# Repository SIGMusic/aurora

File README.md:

Aurora
======

*Wirelessly networked RGB floodlights*

Aurora is a SIGMusic project to build a set of colorful floodlights that can
be used modularly for various projects. These lights are wirelessly controlled
by a Raspberry Pi that accepts clients over the Internet, which allows anyone
to write and run interactive lighting visualizations.

See [the wiki](../../wiki) for info about the hardware, protocol, and for
instructions on building the lights.

Repository layout
-----------------

* The `examples` folder contains sample client applications
* The `firmware` folder contains the Arduino sketch that runs on the lights
* The `hardware` folder contains the Eagle files for the base station shield
  and the logic board in each of the lights
* The `software` folder contains the Python scripts that run on the
  Raspberry Pi and manage the socket servers, scheduler, and radio network

Setup
-----

TODO

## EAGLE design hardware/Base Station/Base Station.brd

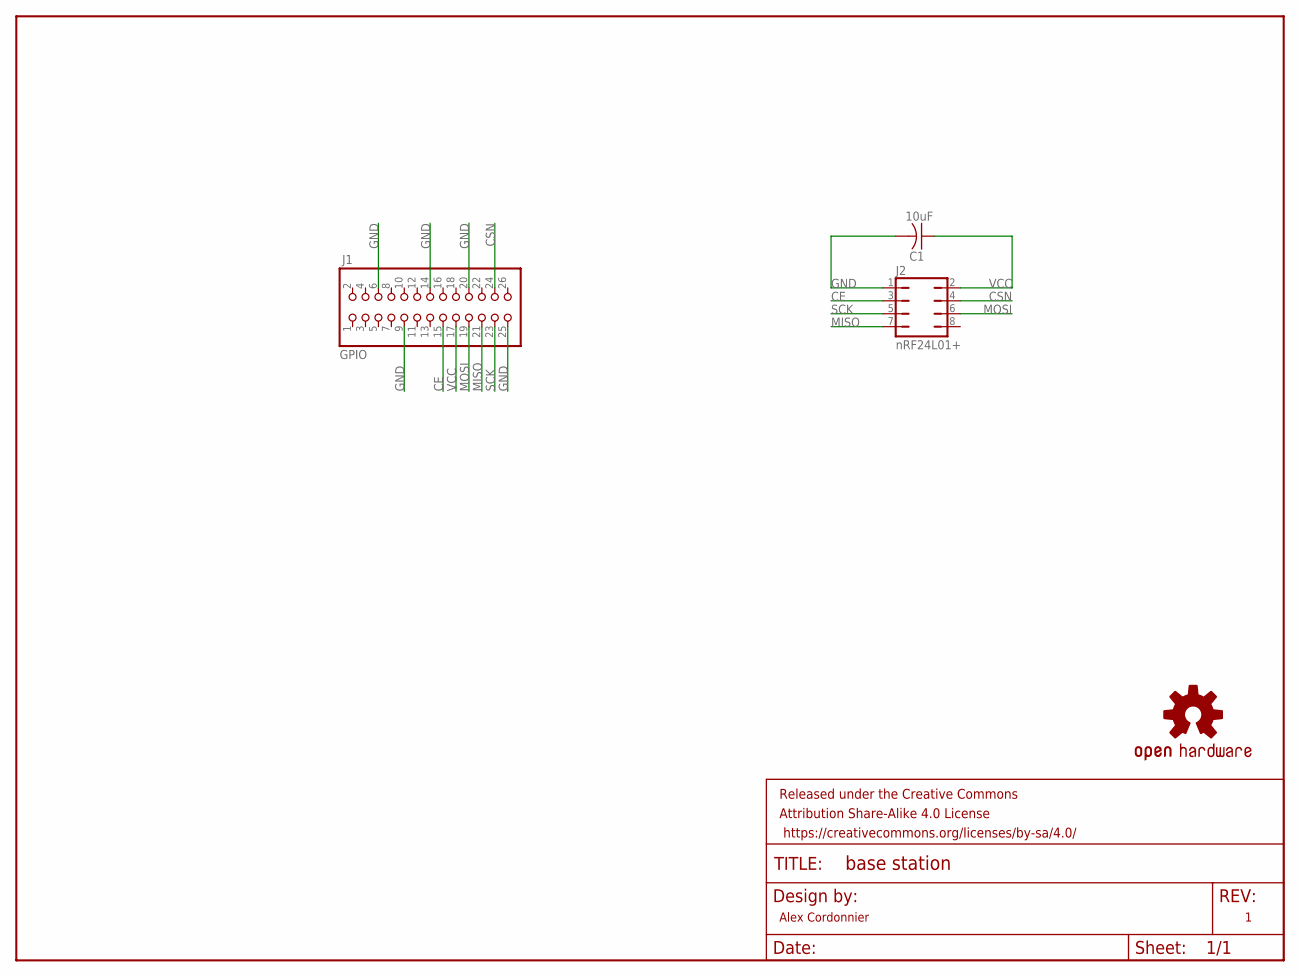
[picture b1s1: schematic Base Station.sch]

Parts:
C1: 10uF; C1206K
FRAME1: FRAME-LETTERNO_PACKAGE; DUMMY
J1: GPIO; 2X13
J2: nRF24L01+; FEMALE-2X4-SMT
LOGO1: OSHW-LOGOS; OSHW-LOGO-S

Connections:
CE: J1.15, J2.3
CSN: J1.24, J2.4
GND: C1.2, J1.6, J1.9, J1.14, J1.20, J1.25, J2.1
MISO: J1.21, J2.7
MOSI: J1.19, J2.6
SCK: J1.23, J2.5
VCC: C1.1, J1.17, J2.2

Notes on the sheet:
Alex Cordonnier

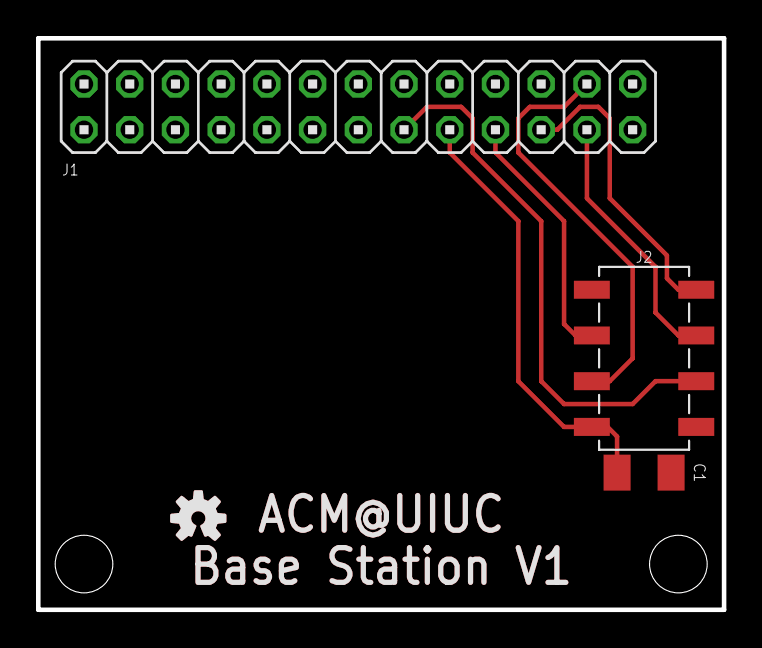
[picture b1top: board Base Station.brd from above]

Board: 2 copper layers, 38.1 x 31.8 mm, 6 parts (0 on the bottom side), 7 nets.

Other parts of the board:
U$1: OSHW-LOGO-S_COPPER

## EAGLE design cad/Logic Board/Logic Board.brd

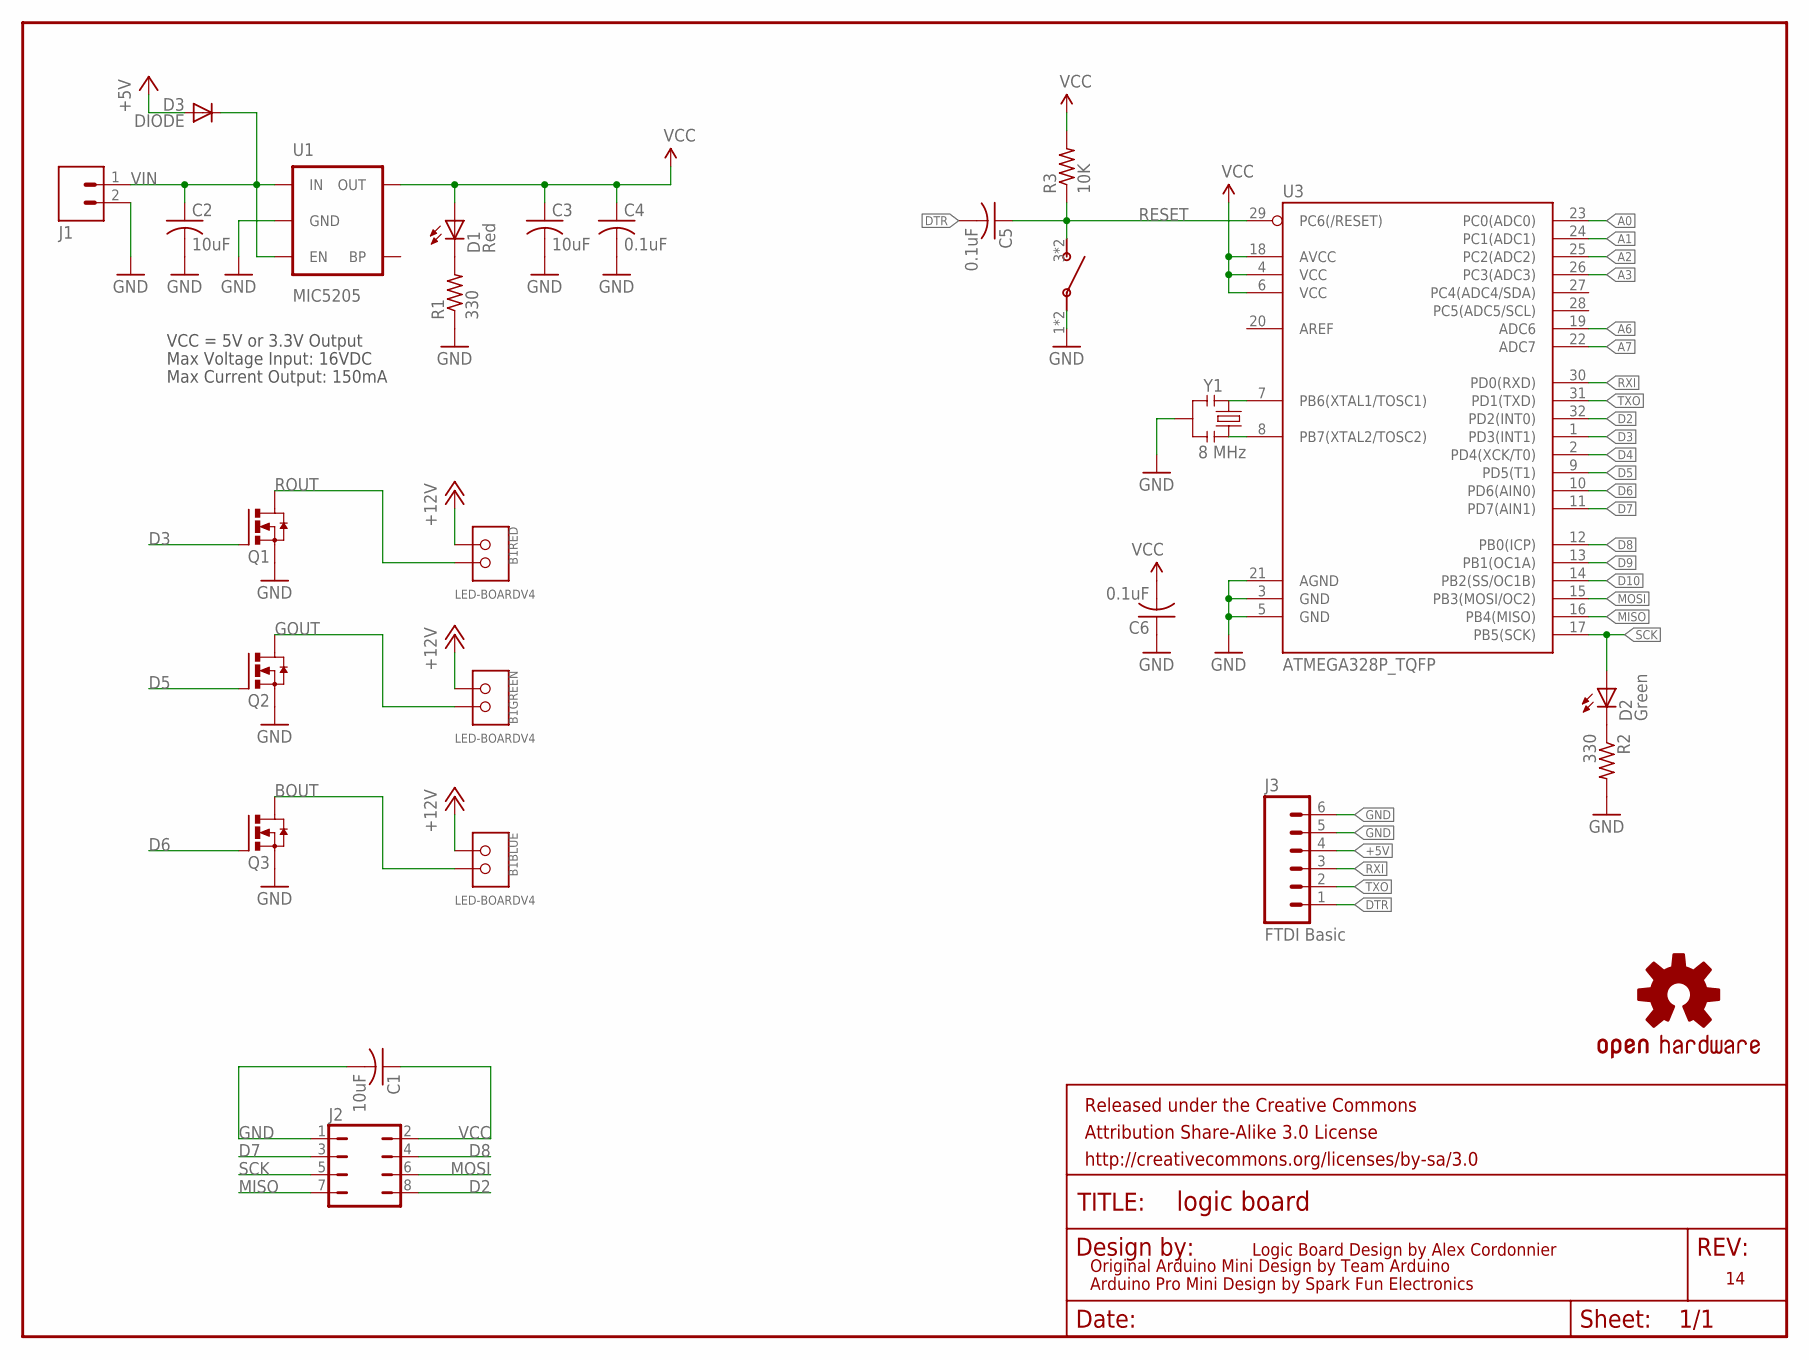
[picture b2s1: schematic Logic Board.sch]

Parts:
B1: LED-BOARDV4; LED_BOARD-V4
C1, C2, C3: 10uF; C1206K
C4, C5, C6: 0.1uF; C1206K
D1: Red; SML1206
D2: Green; SML1206
D3: DIODE; DIODE-1206
FRAME1: FRAME-LETTER; CREATIVE_COMMONS
J1: SCREWTERMINAL
J2: FEMALE-2X4-SMT
J3: FTDI Basic; 1X06_SMD_MALE
LOGO1: OSHW-LOGOS; OSHW-LOGO-S
Q1, Q2, Q3: N-HEXFET-2D_SOT232-; SOT223
R1, R2: 330; R1206
R3: 10K; R1206
S1: TACTILE-BUTTON-PTS525
U1: MIC5205; SOT23-5
U3: ATMEGA328P_TQFP; TQFP32-08
Y1: 8 MHz; RESONATOR-SMD-1:1

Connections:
+5V: D3.P$3 (A), J3.4
A0: U3.23 (PC0(ADC0))
A1: U3.24 (PC1(ADC1))
A2: U3.25 (PC2(ADC2))
A3: U3.26 (PC3(ADC3))
A6: U3.19 (ADC6)
A7: U3.22 (ADC7)
BOUT: B1.B-, B1.B-@1, Q3.2 (D), Q3.4 (D)
D2: J2.8, U3.32 (PD2(INT0))
D3: Q1.1 (G), U3.1 (PD3(INT1))
D4: U3.2 (PD4(XCK/T0))
D5: Q2.1 (G), U3.9 (PD5(T1))
D6: Q3.1 (G), U3.10 (PD6(AIN0))
D7: J2.3, U3.11 (PD7(AIN1))
D8: J2.4, U3.12 (PB0(ICP))
D9: U3.13 (PB1(OC1A))
D10: U3.14 (PB2(SS/OC1B))
DTR: C5.2, J3.1
GND: C1.2, C2.2, C3.2, C4.2, C6.1, J1.2, J2.1, J3.5, J3.6, Q1.3 (S), Q2.3 (S), Q3.3 (S), R1.1, R2.2, S1.1, S1.2 (1), U1.2 (GND), U3.3 (GND), U3.5 (GND), U3.21 (AGND), Y1.2
GOUT: B1.G-, B1.G-@1, Q2.2 (D), Q2.4 (D)
MISO: J2.7, U3.16 (PB4(MISO))
MOSI: J2.6, U3.15 (PB3(MOSI/OC2))
unnamed: U3.8 (PB7(XTAL2/TOSC2)), Y1.3
unnamed: U3.7 (PB6(XTAL1/TOSC1)), Y1.1
unnamed: D2.C, R2.1
unnamed: D1.C, R1.2
RESET: C5.1, R3.1, S1.3, S1.4 (3), U3.29 (PC6(/RESET))
ROUT: B1.R-, B1.R-@1, Q1.2 (D), Q1.4 (D)
RXI: J3.3, U3.30 (PD0(RXD))
SCK: D2.A, J2.5, U3.17 (PB5(SCK))
TXO: J3.2, U3.31 (PD1(TXD))
VCC: C1.1, C3.1, C4.1, C6.2, D1.A, J2.2, R3.2, U1.5 (OUT), U3.4 (VCC), U3.6 (VCC), U3.18 (AVCC)
VIN: B1.B+, B1.B+@2, B1.G+, B1.G+@1, B1.R+, B1.R+@1, C2.1, D3.P$4 (C), J1.1, U1.1 (IN), U1.3 (EN)

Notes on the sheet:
Original Arduino Mini Design by Team Arduino
Arduino Pro Mini Design by Spark Fun Electronics
Max Voltage Input: 16VDC
Max Current Output: 150mA
VCC = 5V or 3.3V Output
Logic Board Design by Alex Cordonnier

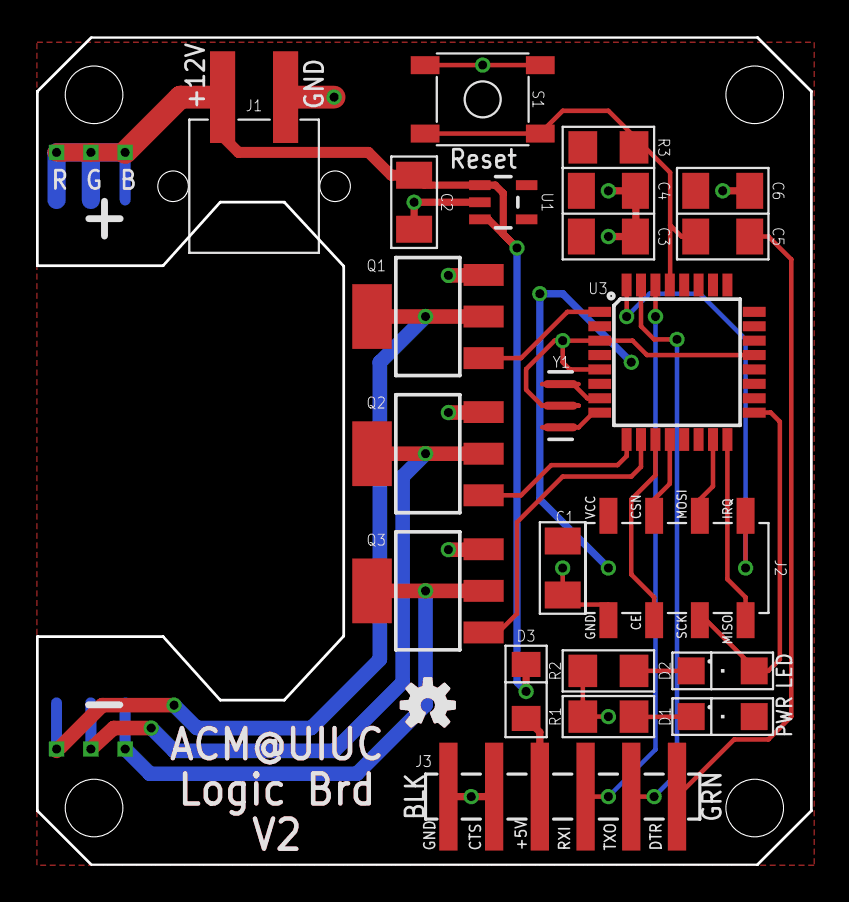
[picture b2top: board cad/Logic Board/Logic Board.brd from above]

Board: 2 copper layers, 43.0 x 46.0 mm, 26 parts (0 on the bottom side), 24 nets.

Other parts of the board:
U$1: OSHW-LOGO-S_COPPER

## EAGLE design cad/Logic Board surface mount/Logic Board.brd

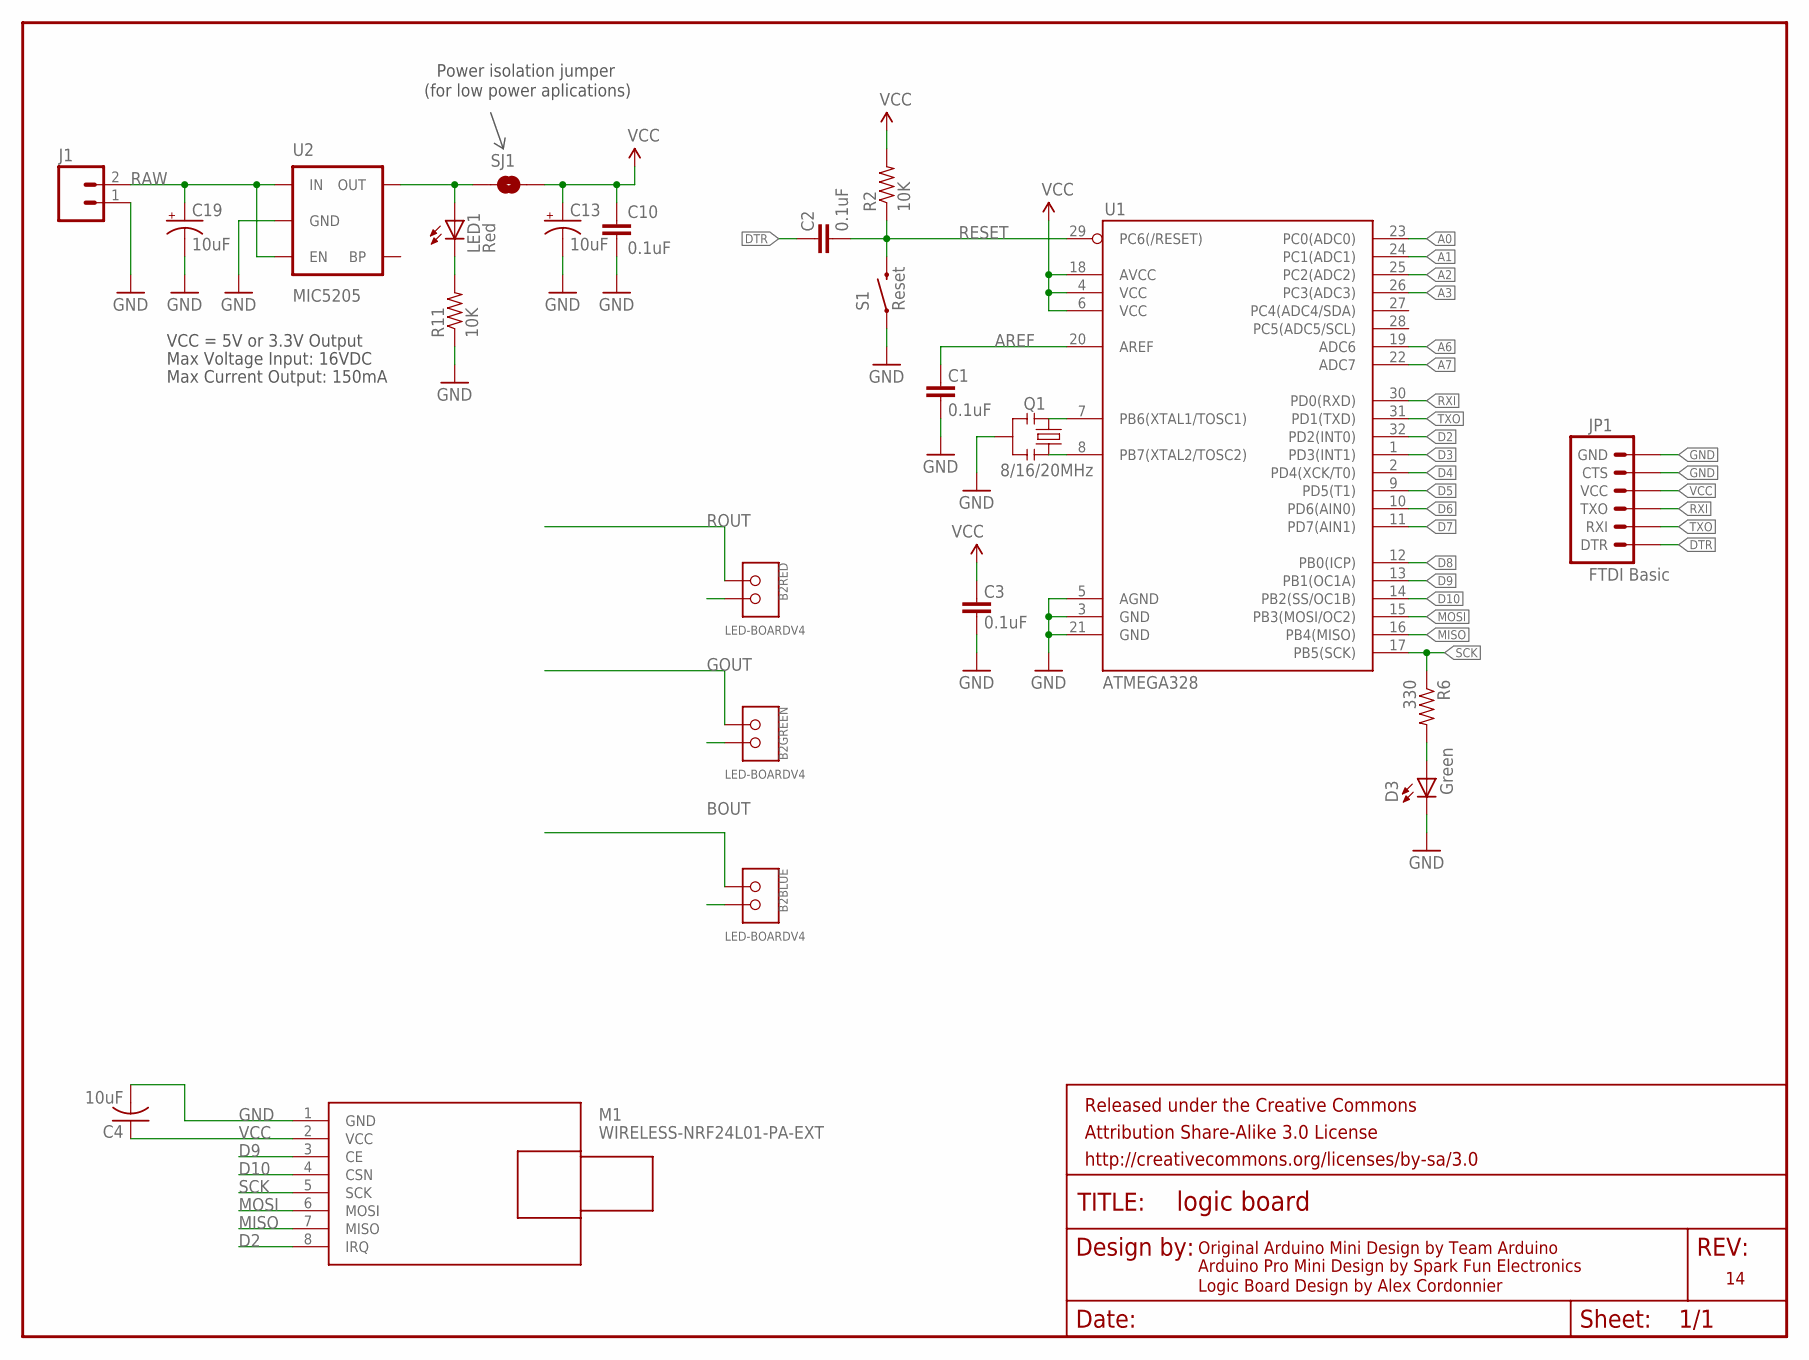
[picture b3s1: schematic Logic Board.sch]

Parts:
B2: LED-BOARDV4; LED_BOARD-V4
C1, C2, C3, C10: 0.1uF; 0603-CAP
C4: 10uF; C1206
C13, C19: 10uF; EIA3216
D3: Green; 0603-LED-ALT1
FRAME1: FRAME-LETTER; CREATIVE_COMMONS
J1: M023.5MM; SCREWTERMINAL-3.5MM-2
JP1: FTDI Basic; 1X06
LED1: Red; 0603-LED-ALT1
M1: WIRELESS-NRF24L01-PA-EXT; WIRELESS-NRD24L01-PA-EXT
Q1: 8/16/20MHz; RESONATOR-SMD-1:1
R2, R11: 10K; 0603-RES
R6: 330; 0603-RES
S1: Reset; TACTILE-SWITCH-SMD-ALT01
SJ1: SOLDERJUMPERNC; SJ_2S
U1: ATMEGA328; TQFP32-08
U2: MIC5205; SOT23-5

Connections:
A0: U1.23 (PC0(ADC0))
A1: U1.24 (PC1(ADC1))
A2: U1.25 (PC2(ADC2))
A3: U1.26 (PC3(ADC3))
A6: U1.19 (ADC6)
A7: U1.22 (ADC7)
AREF: C1.2, U1.20 (AREF)
BOUT: B2.B+, B2.B+@2
D2: M1.8 (IRQ), U1.32 (PD2(INT0))
D3: U1.1 (PD3(INT1))
D4: U1.2 (PD4(XCK/T0))
D5: U1.9 (PD5(T1))
D6: U1.10 (PD6(AIN0))
D7: U1.11 (PD7(AIN1))
D8: U1.12 (PB0(ICP))
D9: M1.3 (CE), U1.13 (PB1(OC1A))
D10: M1.4 (CSN), U1.14 (PB2(SS/OC1B))
DTR: C2.2, JP1.1 (DTR)
GND: C1.1, C3.1, C4.2, C10.2, C13.C (-), C19.C (-), D3.C, J1.1, JP1.5 (CTS), JP1.6 (GND), M1.1 (GND), Q1.2, R11.1, S1.1, S1.2 (1), U1.3 (GND), U1.5 (AGND), U1.21 (GND), U2.2 (GND)
GOUT: B2.G+, B2.G+@1
MISO: M1.7 (MISO), U1.16 (PB4(MISO))
MOSI: M1.6 (MOSI), U1.15 (PB3(MOSI/OC2))
unnamed: Q1.3, U1.8 (PB7(XTAL2/TOSC2))
unnamed: Q1.1, U1.7 (PB6(XTAL1/TOSC1))
unnamed: LED1.A, SJ1.1, U2.5 (OUT)
unnamed: LED1.C, R11.2
unnamed: B2.R-, B2.R-@1
unnamed: D3.A, R6.2
unnamed: B2.G-, B2.G-@1
unnamed: B2.B-, B2.B-@1
RAW: C19.A (+), J1.2, U2.1 (IN), U2.3 (EN)
RESET: C2.1, R2.1, S1.3 (2), S1.4 (2), U1.29 (PC6(/RESET))
ROUT: B2.R+, B2.R+@1
RXI: JP1.3 (TXO), U1.30 (PD0(RXD))
SCK: M1.5 (SCK), R6.1, U1.17 (PB5(SCK))
TXO: JP1.2 (RXI), U1.31 (PD1(TXD))
VCC: C3.2, C4.1, C10.1, C13.A (+), JP1.4 (VCC), M1.2 (VCC), R2.2, SJ1.2, U1.4 (VCC), U1.6 (VCC), U1.18 (AVCC)

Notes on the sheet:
Original Arduino Mini Design by Team Arduino
Arduino Pro Mini Design by Spark Fun Electronics
Max Voltage Input: 16VDC
Max Current Output: 150mA
VCC = 5V or 3.3V Output
Power isolation jumper
(for low power aplications)
Logic Board Design by Alex Cordonnier

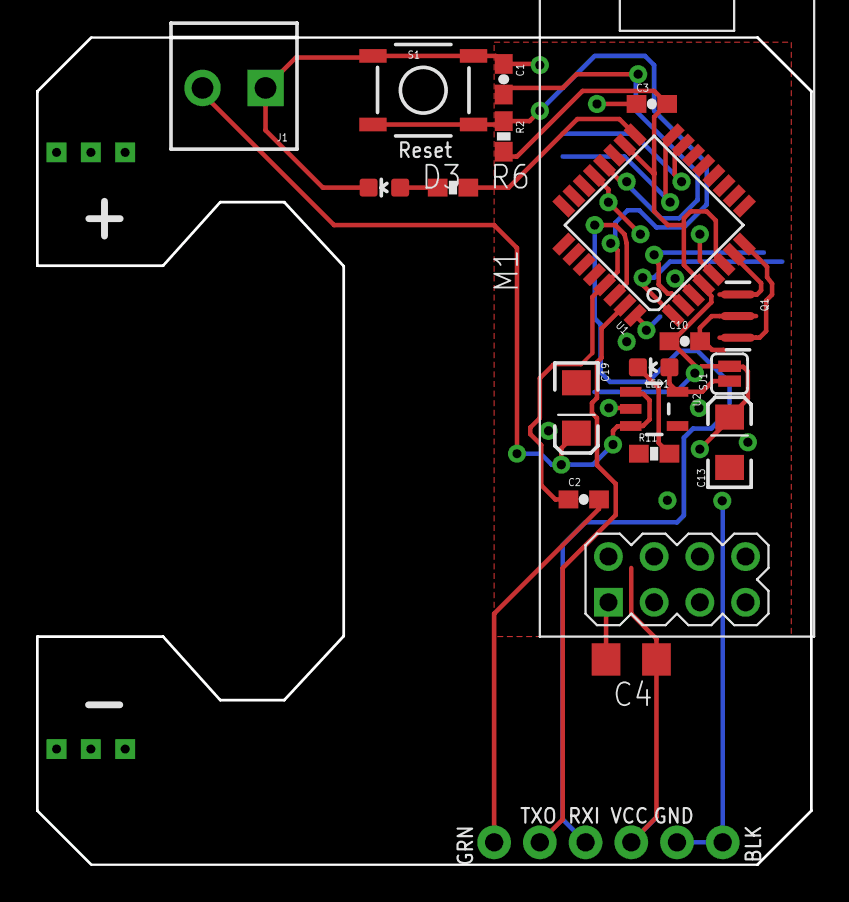
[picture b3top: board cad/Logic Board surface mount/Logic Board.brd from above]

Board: 2 copper layers, 43.0 x 46.0 mm, 22 parts (1 on the bottom side), 25 nets.

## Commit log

2014-11-16 Implemented protocol except channel byte
    Will hopefully discuss the necessity of the channel byte at the next
    dev meeting.
2014-11-16 Added Bluetooth class
    Still working out design issues
2014-12-17 Fixed error response
2014-12-17 Defensive coding
2015-02-01 Added RGB pins, removed Bluetooth class
2015-02-01 Whoops
2015-02-01 Added debugging LED code back
2015-02-08 Added a Comment
2015-02-12 Changed name
2015-02-14 Added License
2015-02-16 Added setup instructions
2015-02-22 Added manager
2015-02-22 Testing git with 2-factor auth - please ignore
2015-02-26 Implemented Light and part of manager (testme!)
    I am rather new to Python, and the Light class is the first one I’ve
    ever written. There are bound to be bugs. I did try to write it to be
    rather robust, though.
    I can’t test on my Mac because pybluez is only compatible with Windows
    and Linux.
2015-02-26 silly syntax error
2015-02-26 Ignore compiled Python classes
2015-03-07 Started a Chrome driver for Bluetooth
2015-03-07 Added external messaging API
2015-03-07 Added some setRGB error checking and fixed sample code
2015-03-07 Added localhost as externally connectable
2015-03-08 Fixed manager
2015-03-08 Removed debug code
2015-03-08 Cycle hue in each light
2015-03-11 Remove Chrome extension from master
2015-03-11 Updated read for websocket-client
2015-03-12 Added error checking
2015-03-12 Fixed socket connection issue
2015-03-12 Syntax error
2015-03-12 More robust light discovery and connection
2015-03-12 Added websocket connection callbacks
2015-03-12 Added JSON parsing
2015-03-13 Lots o changes
2015-03-13 Got websocket working, comets still broken
2015-03-13 Removed SimpleWebSocketServer
2015-03-13 Some semblance of working
2015-03-13 Working marginally
2015-03-13 Fixed physics
2015-03-13 twinkle twinkle
2015-03-13 twinkle twinkle part iv
2015-03-13 twinkle twinkle part v
2015-03-13 Updated readme to include Tornado instructions
2015-03-23 Attempt to use L2CAP when possible
2015-04-12 Multithreaded!
2015-04-12 Updated readme for discovery
2015-07-08 Initial implementation using nRF24L01+
    Don’t have an Arduino on hand, so this code is completely untested.
2015-07-10 Fixed pins, improved code style
2015-07-11 Rethought network architecture
    Each light now listens on two addresses: its individual endpoint
    address and the broadcast address. All lights communicate to the base
    station on one address.
2015-07-12 Started rewriting manager
2015-07-12 Fixed a few minor Python issues
2015-07-12 Fixed function order
2015-07-12 Must convert to string to write
2015-07-12 Removed annoying space
2015-07-12 Now using big-endian
2015-07-12 Use structs instead of bytearray
2015-07-12 Fixed dictionarary key
2015-07-12 Move to C++ for better performance
    The goal is to eventually implement WebSockets as the only public way
    to control the lights.
2015-07-12 Fixing bugs
2015-07-12 Pointers.
2015-07-12 Fixed casting issue
2015-07-12 Fixed C++ version
2015-07-12 Removed install target
2015-07-12 Adding in websockets
2015-07-12 hooray websockets
2015-07-14 Got websockets to compile
2015-07-14 Removed broadcast capability
    This feature had few potential use cases and conflicted with the
    upcoming color calibration feature.
2015-07-14 Filter connections by protocol
2015-07-14 Forgot function prototype
2015-07-14 Compiler error
2015-07-14 First attempt at websocket responses
2015-07-14 Corrected a few missteps
2015-07-14 Hopefully better command processing
2015-07-14 Fixed format specifiers
2015-07-14 Implemented list and discover
2015-07-14 Forgot to implement setRGB
2015-07-14 Use vector of bools instead of array
2015-07-15 Added new temperature and uptime commands
2015-07-15 Silly mistakes
2015-07-15 Turns out verbose is nice for debugging
2015-07-18 C++ified (untested, probably broken)
2015-07-18 Forgot to rename include
2015-07-18 Fixed some compile errors
2015-07-18 Another bug
2015-07-18 More compile errors
2015-07-18 Mismatched function prototypes
2015-07-18 Namespace
2015-07-18 All the little things
2015-07-18 These should be static
2015-07-18 Makefile changes and compile error fix
2015-07-18 Fixed Makefile
2015-07-18 Static initialization weirdness
2015-07-19 Added ping command
2015-07-19 Echo instead of responding OK
2015-08-07 Fixed pin numbers
    I think
2015-08-08 Added radio debugging info
2015-08-08 Forgot class namespace
2015-08-08 Fixed Makefile and removed printDetails
    The Radio constructor already calls printDetails. No need for an
    additional method.
2015-08-08 Optimized Makefile
2015-08-22 Added Eagle files
2015-08-22 Moved files to src folder
2015-10-04 Updated board layouts
2015-12-03 Started new SMD logic board
2015-12-03 Updated board
2015-12-03 More board layout changes
2015-12-04 More tweaks
2015-12-04 Added improved board layout
2015-12-05 Fixed airwires & some design rules
2015-12-05 Rearranged some traces
2015-12-05 Cleaned up a bit
2015-12-05 Made ground connection clearer
2016-01-16 Fixed DRC error
2016-01-18 Fixed resistors
2016-01-18 Added MOSFETS
2016-01-18 Fixed overlap
2016-01-18 Fixed MOSFETS
2016-01-18 Switched header to SMT
2016-01-19 Fixed screw terminal
2016-01-19 Renumbered parts
2016-01-19 Changed capacitor package
2016-01-19 Added OSHW logo
2016-01-19 Increased fonts
2016-01-19 Improved routing near reset button
2016-01-20 Fixed alignment
2016-01-20 Cleaned up schematic
2016-01-21 Fixed incorrect button package
2016-01-21 Added names and outlines
2016-01-21 Added mounting holes
2016-01-22 Updated base station
2016-01-22 Removed old logic board versions
2016-01-22 Rerouted some traces
2016-01-22 Fixed disconnected ground nets
2016-01-22 Fixed incorrect microcontroller
2016-01-22 Moved around RX and TX
2016-01-23 Replaced 2x4 header part
2016-01-23 Adjusted resonator position
2016-01-23 Adjusted RX and TX traces
2016-01-23 Fixed silkscreen
2016-01-23 More silkscreen tweaks
2016-01-23 Adjusted trace position
2016-01-23 Fixed part labels
2016-01-24 Rotated the ATmega
2016-01-24 Fixed pin assignments and cleaned up code
2016-01-25 Added 3.3V to VCC label
2016-01-28 Some minor rerouting
2016-01-28 More routing changes
2016-01-29 Minor adjustments
2016-02-01 Separated server process from radio process
2016-02-06 Major refactoring into Radio and Server
2016-02-07 Added lock for connected list
2016-02-07 More refactoring
2016-02-08 Remove address hashing
2016-02-14 Removed header from message format
2016-02-14 Improved temperature calculation
2016-02-15 Fixed pins and minor improvements
2016-02-17 Modified protocol and power issue workaround
2016-02-18 First attempt. Low reliability so far.
2016-02-19 Better, but loses sync quickly. Periodic sync makes it worse?
2016-02-20 Fixed MOSFET logic and added FTDI VCC diode
2016-02-20 Improved layout
2016-02-20 Adjusted mounting holes
2016-02-22 Rearranged & rerouted more
2016-02-22 Some more adjustments
2016-02-22 Fixed frame
2016-02-22 Some final adjustments
2016-02-23 Actual last changes this time
2016-02-28 Debugging
2016-02-28 Removed everything not needed for EOH
2016-02-29 Improved accuracy with micros() since millis() is being weird
2016-03-01 Still improving accuracy
2016-03-01 Getting better
2016-03-06 Got base station and receiver clocks synced
2016-03-06 Still gets out of sync when actual channel hopping is enabled
2016-03-06 Use signals and interrupts
2016-03-08 Improved serial interface. Mysteriously large error rate, though.
2016-03-08 Refactoring
2016-03-10 Fixed LED initialization
2016-05-07 Made transmitFrame not a signal handler
2016-05-09 Started websocket implementation
2016-05-09 Fixed memory bug
2016-05-09 Implemented receiving, fixed bugs
2016-05-10 Implemented send, close, ping/pong
2016-05-16 Switched server over to new web socket implementation
2016-05-17 Added initial UDP server support
2016-05-18 Fixed some race conditions
2016-05-20 Fixed IPv4/6 issue
2016-07-10 Removed optimizations so it compiles faster
2016-07-24 Restructured manager into multiple services
2016-07-24 Migrating to Python
2016-07-30 Added initial radio and scheduler classes
2016-07-30 Removed unnecessary include folder
2016-07-31 Implemented periodic frame transmission and fixed formatting
2016-07-31 Pythonified address generation
2016-07-31 Added removeJob and job IDs
2016-07-31 Added colors mutex and improved debugging
2016-07-31 Pythonified address assertion
2016-08-01 Started implementing scheduler
2016-08-07 Made RF24 dependency optional for faster local testing
2016-08-07 Fixed locking on _jobs
2016-08-10 Improved logging
2016-08-13 Fixed some logging things
2016-08-13 Added light number
2016-08-13 Fixed several scheduler issues
2016-08-13 Privatized rf_address
2016-09-01 Fixed job locking
2016-09-10 Added DS_Store to gitignore
2016-09-15 Started websocket server

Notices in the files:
parts and their libraries:
SparkFun-Aesthetics: Licensing: Creative Commons ShareAlike 4.0 International - https://creativecommons.org/licenses/by-sa/4.0
SparkFun-Aesthetics: Released under the Creative Commons Attribution Share-Alike 4.0 License
SparkFun-Aesthetics: https://creativecommons.org/licenses/by-sa/4.0
